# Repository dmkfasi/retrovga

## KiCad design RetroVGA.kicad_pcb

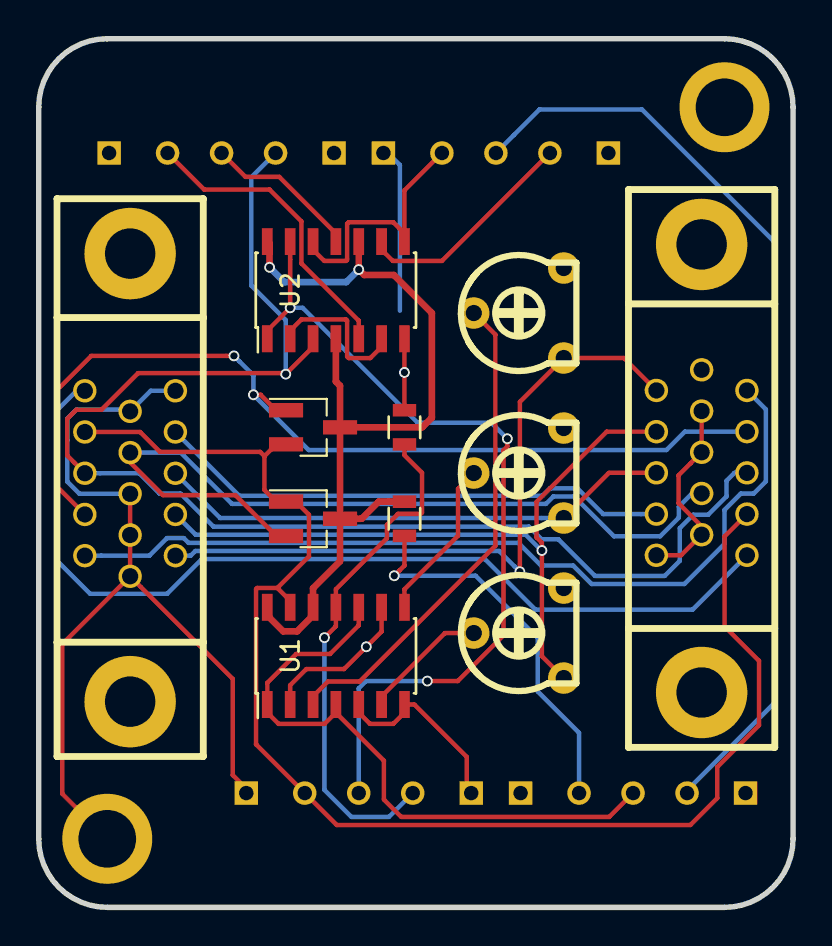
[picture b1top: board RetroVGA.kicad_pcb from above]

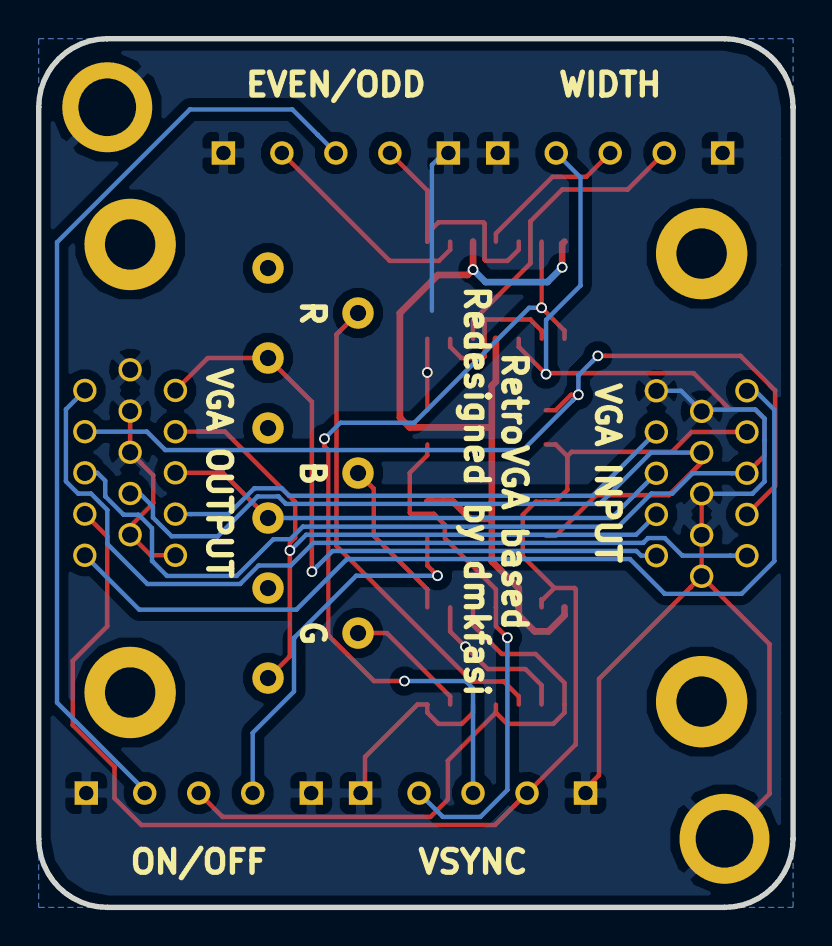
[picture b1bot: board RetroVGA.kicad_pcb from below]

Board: 2 copper layers, 41.9 x 48.3 mm, 15 parts (4 on the bottom side), 25 nets.

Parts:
D1, D2: BAT54C; SOT-23_Handsoldering
J1: VGA INPUT; ds1038-15f
J2: VGA OUTPUT; ds1038-15f
R1, R2: 100K; R_0805
R3: R; trimmer_piher_pt6xv
R4: G; trimmer_piher_pt6xv
R5: B; trimmer_piher_pt6xv
SW1: ON/OFF; switch-ss12f23
SW2: EVEN/ODD; switch-ss12f23
SW3: WIDTH; switch-ss12f23
SW4: VSYNC; switch-ss12f23
U1: 74LS125; SOIC-14_3.9x8.7mm_Pitch1.27mm
U2: 74HC74; SOIC-14_3.9x8.7mm_Pitch1.27mm

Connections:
/#QB: SW2.3, U2.8, U2.12
/#VSYNC: R2.1, SW4.3, U1.11
/BLUE: J1.3, J2.3, R5.1
/CLK: SW3.2, U2.11
/CLR: SW4.2, U2.1, U2.13
/GREEN: J1.2, J2.2, R4.1
/HSYNC: J1.13, J2.13, SW3.1, U2.3
/ID0: J1.11, J2.11
/P_BLUE: R5.2, U1.8
/P_GREEN: R4.2, U1.6
/P_RED: R3.2, U1.3
/QA: SW3.3, U2.5
/QB: SW2.1, U2.9
/RED: J1.1, J2.1, R3.1
/RES: J1.4, J2.4
/SCL: J1.15, J2.15
/SDA: D2.1, J1.12, J2.12
/STATE: SW1.2, U1.1, U1.4, U1.10
/VGA5V: D1.2, J1.9, J2.9
/VSYNC: D1.1, D2.2, J1.14, J2.14, SW4.1, U1.13
GND: J1.5, J1.6, J1.7, J1.8, J1.10, J2.5, J2.6, J2.7, J2.8, J2.10, R2.2, U1.2, U1.5, U1.7, U1.9, U2.7
unnamed: R1.2, SW1.1
unnamed: SW1.3, SW2.2
unnamed: U2.2, U2.6
VCC: D1.3, D2.3, R1.1, U1.12, U1.14, U2.4, U2.10, U2.14

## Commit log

2017-01-18 Updated Gerber files, didn't include soldermask layer before, fixing now.
2017-01-20 Edge Cut layer
2017-01-20 Production Gerber files, all in one package
2017-01-20 Latest saved version for production
2017-02-19 Now using Walter's 3D shape for VGA terminal. It does not fit properly, but still reflects overall look
